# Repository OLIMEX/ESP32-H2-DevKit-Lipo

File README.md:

# ESP32-H2-DevKit-Lipo
Development board for ESP32-H2 SOC with BLE5 Matter, Thread, Zigbee

https://www.olimex.com/Products/IoT/ESP32-H2/ESP32-H2-DevKit-LiPo/open-source-hardware

Features:

* ESP32-H1-MINI-1-N4 module
* USB-C with USB to Serial converter for programming / debugging
* USB-C connected directly to ESP32-H2
* LiPo battery charger and connector
* pUEXT connector
* Qwiic/Stemma connector
* Reset button
* User button
* User LED
* all GPIOs available on two headers at 25.4 mm space
* operating temperature -40+85C
* Dimensions: 48 x 25 mm

## Licenses

* Hardware is released under CERN Open Hardware Licence Version 2 - Strongly Reciprocal, all silkscreen credits to Olimex should remain;
* Software is released under GPL3 Licensee
* Documentation is released under CC BY-SA 3.0

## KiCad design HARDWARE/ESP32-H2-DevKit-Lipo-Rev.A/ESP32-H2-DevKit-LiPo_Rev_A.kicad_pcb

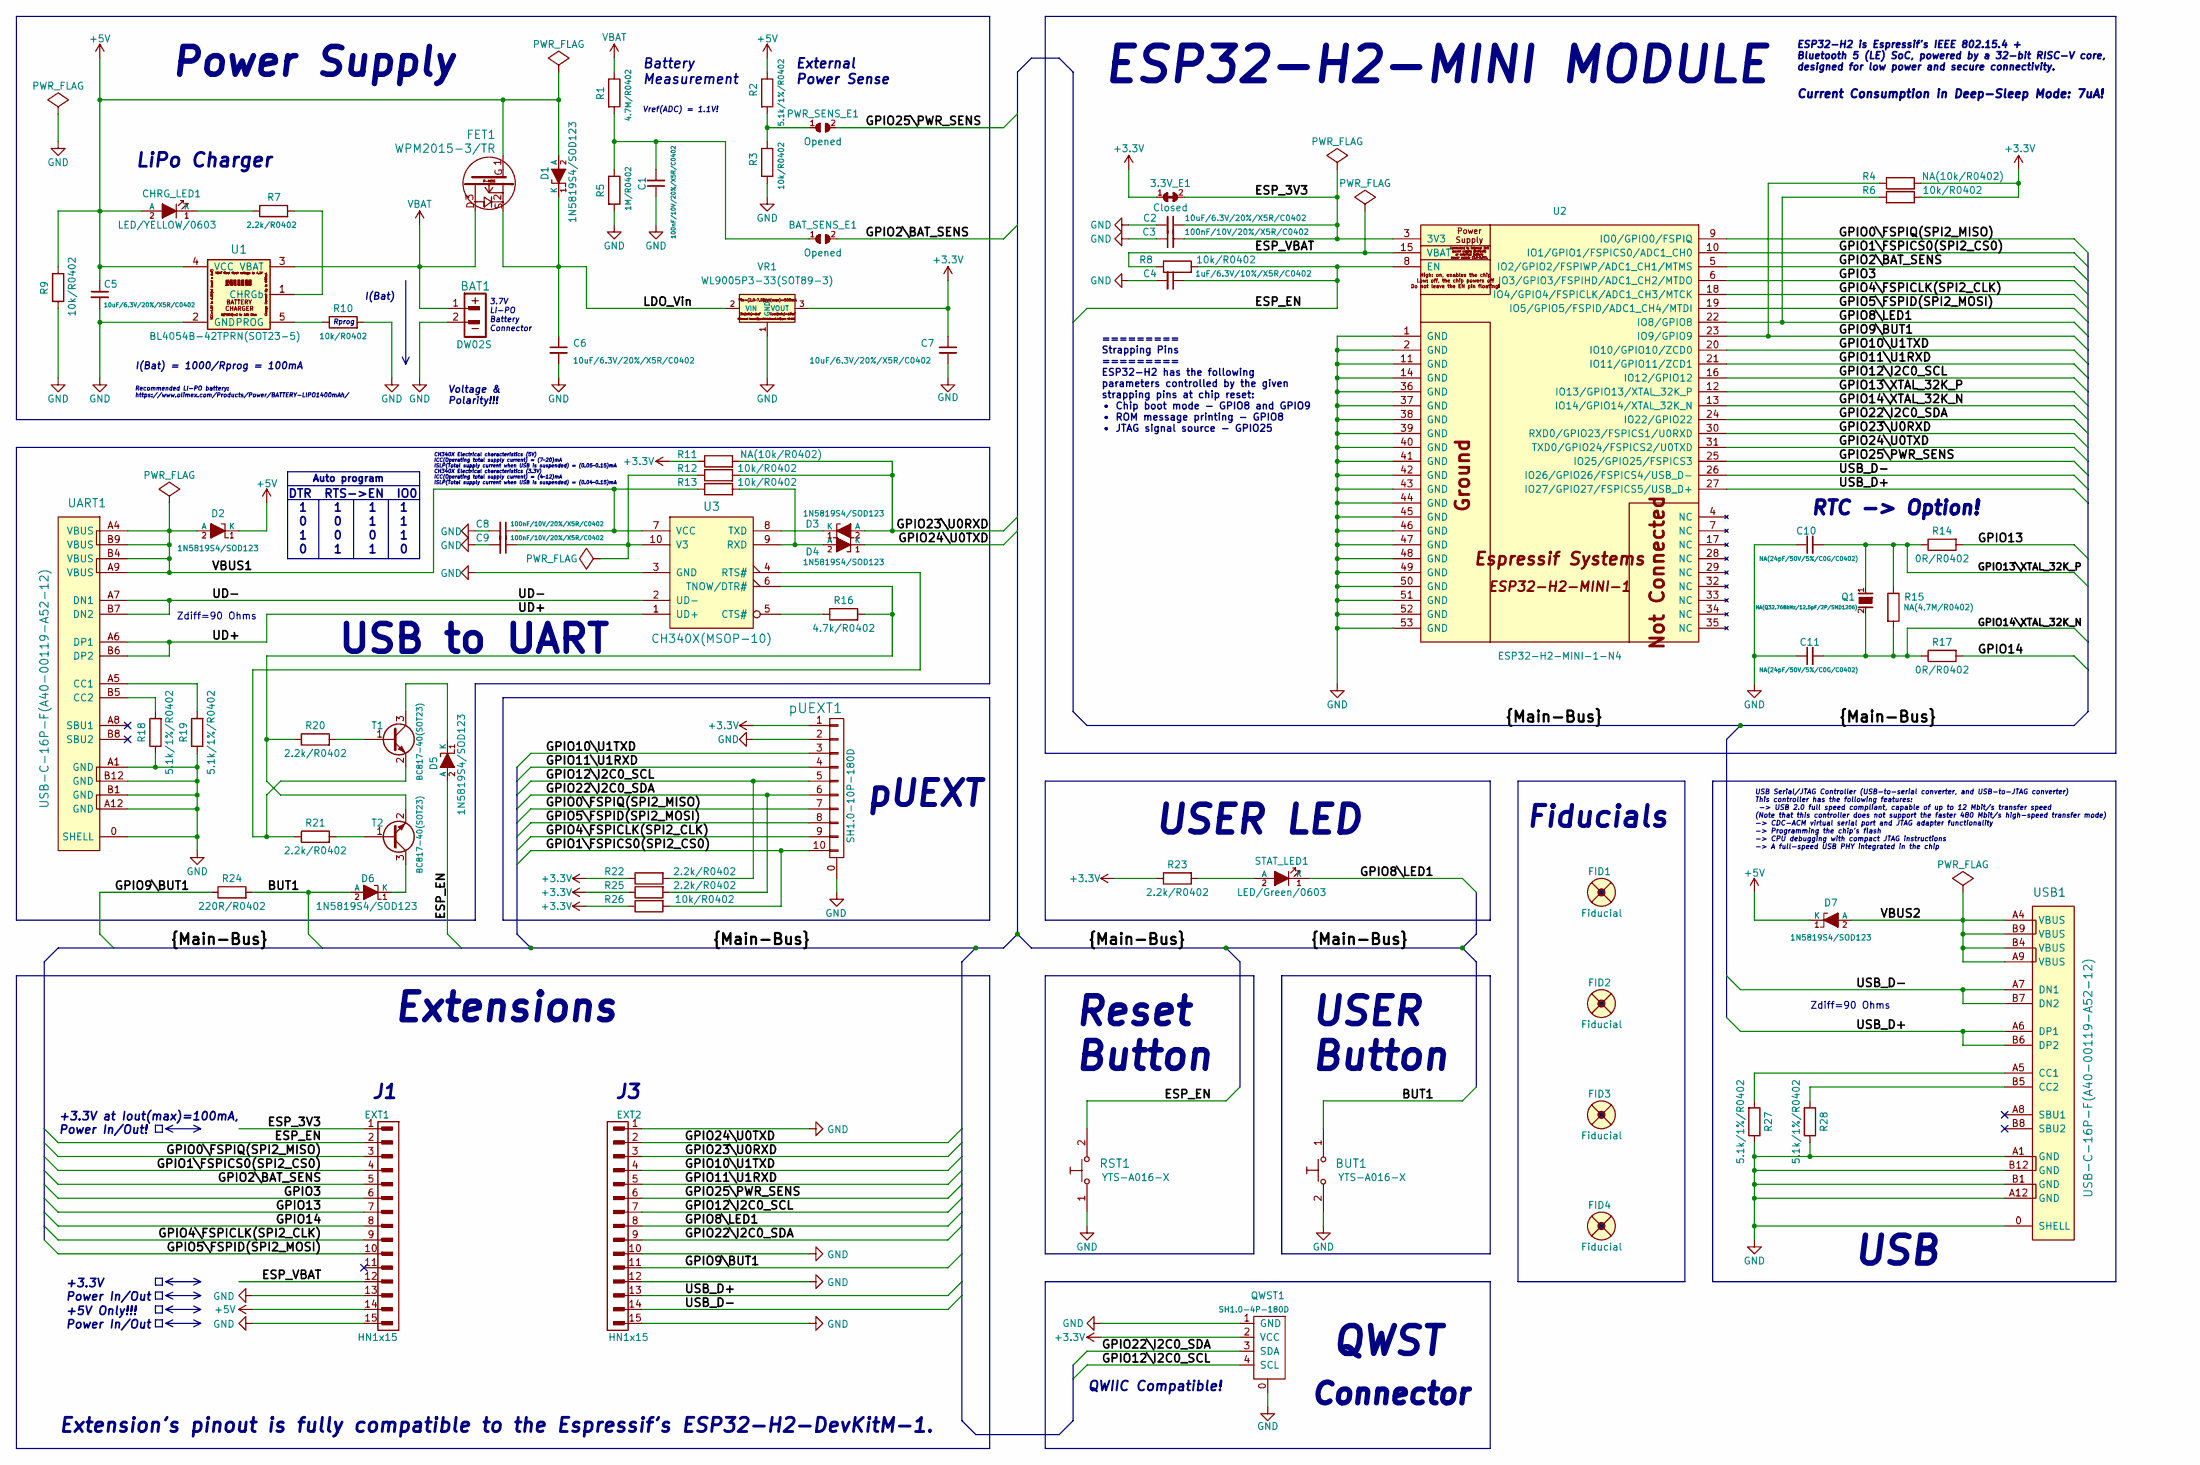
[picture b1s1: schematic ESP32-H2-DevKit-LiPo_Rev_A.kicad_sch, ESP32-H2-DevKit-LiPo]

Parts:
3.3V_E1: Closed; SJ_Closed
BAT1: DW02S; LIPO_BAT_VERTICAL_DW02S
BAT_SENS_E1: Opened; SJ
BUT1: YTS-A016-X
C1, C3, C8, C9: 100nF/10V/20%/X5R/C0402; C_0402_5MIL_DWS
C2, C5, C6, C7: 10uF/6.3V/20%/X5R/C0402; C_0402_5MIL_DWS
C4: 1uF/6.3V/10%/X5R/C0402; C_0402_5MIL_DWS
C10, C11: NA(24pF/50V/5%/C0G/C0402); C_0402_5MIL_DWS
CHRG_LED1: LED/YELLOW/0603; LED_0603_KA
D1, D2, D3, D4, D5, D6, D7: 1N5819S4/SOD123; SOD-123_1C-2A_KA
EXT1, EXT2: HN1x15
FET1: WPM2015-3/TR; SOT23
FID1, FID2, FID3: Fiducial; Fiducial1x3
FID4: Fiducial; Fiducial1x3_Paste
PWR_SENS_E1: Opened; SJ
Q1: NA(Q32.768kHz/12.5pF/2P/SMD1206); CM7V-T1A(Crystal_Package-1206_3.20x1.50x0.65mm)
QWST1: SH1.0-4P-180D; BM04B-SRSS-TB
R1: 4.7M/R0402; R_0402_5MIL_DWS
R2, R18, R19, R27, R28: 5.1k/1%/R0402; R_0402_5MIL_DWS
R3, R6, R8, R9, R10, R12, R13, R26: 10k/R0402; R_0402_5MIL_DWS
R4, R11: NA(10k/R0402); R_0402_5MIL_DWS
R5: 1M/R0402; R_0402_5MIL_DWS
R7, R20, R21, R22, R23, R25: 2.2k/R0402; R_0402_5MIL_DWS
R14, R17: 0R/R0402; R_0402_5MIL_DWS
R15: NA(4.7M/R0402); R_0402_5MIL_DWS
R16: 4.7k/R0402; R_0402_5MIL_DWS
R24: 220R/R0402; R_0402_5MIL_DWS
RST1: YTS-A016-X
STAT_LED1: LED/Green/0603; LED_0603_KA
T1, T2: BC817-40(SOT23); SOT23
U1: BL4054B-42TPRN(SOT23-5); SOT-23-5
U2: ESP32-H2-MINI-1-N4; ESP32-­C3-­MINI­-1
U3: CH340X(MSOP-10); MSOP-10_Pitch-0.5mm_3.00x3.00x1.00mm
UART1: USB-C-16P-F(A40-00119-A52-12); USB2.0_TYPE-C(A40-00119-A52-12)_Paste
USB1: USB-C-16P-F(A40-00119-A52-12); USB2.0_TYPE-C(A40-00119-A52-12)_Paste
VR1: WL9005P3-33(SOT89-3); SOT89-3
pUEXT1: SH1.0-10P-180D; BM10B-SRSS-TB

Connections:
+3.3V: 3.3V_E1.1, C7.1, QWST1.2 (VCC), R4.2, R6.1, R11.1, R22.1, R23.1, R25.1, R26.1, VR1.3 (VOUT), pUEXT1.1
+5V: C5.1, CHRG_LED1.2 (A), D1.2 (A), D2.1 (K), D7.1 (K), EXT1.14, FET1.1, R2.1, R9.1, U1.4 (VCC)
/BUT1: BUT1.1, D6.2 (A), R24.2
/ESP_3V3: 3.3V_E1.2, C2.1, C3.2, EXT1.1, U2.3 (3V3)
/ESP_EN: C4.1, D5.2 (A), EXT1.2, R8.2, RST1.2, U2.8 (EN)
/ESP_VBAT: EXT1.12, R8.1, U2.15 (VBAT)
/GPIO0\FSPIQ(SPI2_MISO): EXT1.3, U2.9 (IO0/GPIO0/FSPIQ), pUEXT1.7
/GPIO1\FSPICS0(SPI2_CS0): EXT1.4, R26.2, U2.10 (IO1/GPIO1/FSPICS0/ADC1_CH0), pUEXT1.10
/GPIO2\BAT_SENS: BAT_SENS_E1.2, EXT1.5, U2.5 (IO2/GPIO2/FSPIWP/ADC1_CH1/MTMS)
/GPIO3: EXT1.6, U2.6 (IO3/GPIO3/FSPIHD/ADC1_CH2/MTDO)
/GPIO4\FSPICLK(SPI2_CLK): EXT1.9, U2.18 (IO4/GPIO4/FSPICLK/ADC1_CH3/MTCK), pUEXT1.9
/GPIO5\FSPID(SPI2_MOSI): EXT1.10, U2.19 (IO5/GPIO5/FSPID/ADC1_CH4/MTDI), pUEXT1.8
/GPIO8\LED1: EXT2.8, R6.2, STAT_LED1.1 (K), U2.22 (IO8/GPIO8)
/GPIO9\BUT1: EXT2.11, R4.1, R24.1, U2.23 (IO9/GPIO9)
/GPIO10\U1TXD: EXT2.4, U2.20 (IO10/GPIO10/ZCD0), pUEXT1.3
/GPIO11\U1RXD: EXT2.5, U2.21 (IO11/GPIO11/ZCD1), pUEXT1.4
/GPIO12\I2C0_SCL: EXT2.7, QWST1.4 (SCL), R22.2, U2.16 (IO12/GPIO12), pUEXT1.5
/GPIO13: EXT1.7, R14.2
/GPIO13\XTAL_32K_P: C10.2, Q1.1, R14.1, R15.1, U2.12 (IO13/GPIO13/XTAL_32K_P)
/GPIO14: EXT1.8, R17.2
/GPIO14\XTAL_32K_N: C11.2, Q1.2, R15.2, R17.1, U2.13 (IO14/GPIO14/XTAL_32K_N)
/GPIO22\I2C0_SDA: EXT2.9, QWST1.3 (SDA), R25.2, U2.24 (IO22/GPIO22), pUEXT1.6
/GPIO23\U0RXD: D3.2 (A), EXT2.3, R11.2, R12.2, U2.30 (RXD0/GPIO23/FSPICS1/U0RXD)
/GPIO24\U0TXD: D4.1 (K), EXT2.2, U2.31 (TXD0/GPIO24/FSPICS2/U0TXD)
/GPIO25\PWR_SENS: EXT2.6, PWR_SENS_E1.2, U2.25 (IO25/GPIO25/FSPICS3)
/LDO_Vin: C6.1, D1.1 (K), FET1.2, VR1.2 (VIN)
/UD+: U3.1 (UD+), UART1.A6 (DP1), UART1.B6 (DP2)
/UD-: U3.2 (UD-), UART1.A7 (DN1), UART1.B7 (DN2)
/USB_D+: EXT2.13, U2.27 (IO27/GPIO27/FSPICS5/USB_D+), USB1.A6 (DP1), USB1.B6 (DP2)
/USB_D-: EXT2.14, U2.26 (IO26/GPIO26/FSPICS4/USB_D-), USB1.A7 (DN1), USB1.B7 (DN2)
/VBUS1: C8.1, D2.2 (A), R13.1, U3.7 (VCC), UART1.A4 (VBUS), UART1.A9 (VBUS), UART1.B4 (VBUS), UART1.B9 (VBUS)
/VBUS2: D7.2 (A), USB1.A4 (VBUS), USB1.A9 (VBUS), USB1.B4 (VBUS), USB1.B9 (VBUS)
GND: BAT1.2, BUT1.2, C1.1, C2.2, C3.1, C4.2, C5.2, C6.2, C7.2, C8.2, C9.2, C10.1, C11.1, EXT1.13, EXT1.15, EXT2.1, EXT2.10, EXT2.12, EXT2.15, QWST1.0, QWST1.1 (GND), R3.2, R5.2, R9.2, R10.2, R18.1, R19.1, R27.1, R28.1, RST1.1, U1.2 (GND), U2.1 (GND), U2.2 (GND), U2.11 (GND), U2.14 (GND), U2.36 (GND), U2.37 (GND), U2.38 (GND), U2.39 (GND), U2.40 (GND), U2.41 (GND), U2.42 (GND), U2.43 (GND), U2.44 (GND), U2.45 (GND), U2.46 (GND), U2.47 (GND), U2.48 (GND), U2.49 (GND), U2.50 (GND), U2.51 (GND), U2.52 (GND), U2.53 (GND), U3.3 (GND), UART1.0 (SHELL), UART1.A1 (GND), UART1.A12 (GND), UART1.B1 (GND), UART1.B12 (GND), USB1.0 (SHELL), USB1.A1 (GND), USB1.A12 (GND), USB1.B1 (GND), USB1.B12 (GND), VR1.1 (GND), pUEXT1.0, pUEXT1.2
unnamed: BAT_SENS_E1.1, C1.2, R1.2, R5.1
unnamed: CHRG_LED1.1 (K), R7.1
unnamed: D3.1 (K), U3.8 (TXD)
unnamed: D4.2 (A), R13.2, U3.9 (RXD)
unnamed: D5.1 (K), T1.3 (C)
unnamed: D6.1 (K), T2.3 (C)
unnamed: PWR_SENS_E1.1, R2.2, R3.1
unnamed: R23.2, STAT_LED1.2 (A)
unnamed: R20.2, T1.1 (B)
unnamed: R21.1, T1.2 (E), U3.4 (RTS#)
unnamed: R21.2, T2.1 (B)
unnamed: R16.2, R20.1, T2.2 (E), U3.6 (TNOW/DTR#)
unnamed: R7.2, U1.1 (CHRGb)
unnamed: R10.1, U1.5 (PROG)
unnamed: R16.1, U3.5 (CTS#)
unnamed: C9.1, R12.1, U3.10 (V3)
unnamed: R19.2, UART1.A5 (CC1)
unnamed: R18.2, UART1.B5 (CC2)
unnamed: R27.2, USB1.A5 (CC1)
unnamed: R28.2, USB1.B5 (CC2)
VBAT: BAT1.1, FET1.3, R1.1, U1.3 (VBAT)

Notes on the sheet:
pUEXT
I(Bat) = 1000/Rprog = 100mA
DTR RTS->EN IO0
I(Bat)
========= Strapping Pins ========= ESP32-H2 has the following parameters controlled by the given strapping pins at chip reset: • Chip boot mode - GPIO8 and GPIO9 • ROM message printing - GPIO8 • JTAG signal source - GPIO25
LiPo Charger
External Power Sense
USB
USB to UART
Vref(ADC) = 1.1V!
RTC -> Option!
Reset Button
Extensions
USER LED
Zdiff=90 Ohms
Fiducials
Extension's pinout is fully compatible to the Espressif's ESP32-H2-DevKitM-1.
Auto program
CH340X Electrical characteristics (5V) ICC(Operating total supply current) = (7~20)mA ISLP(Total supply current when USB is suspended) = (0.05~0.15)mA CH340X Electrical characteristics (3.3V) ICC(Operating total supply current) = (4~12)mA ISLP(Total supply current when USB is suspended) = (0.04~0.1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
+5V Only!!! Power In/Out
Rprog
Battery Measurement
QWST
ESP32-H2-MINI MODULE
USB Serial/JTAG Controller (USB-to-serial converter, and USB-to-JTAG converter) This controller has the following features: -> USB 2.0 full speed compliant, capable of up to 12 Mbit/s transfer speed (Note that this controller does not support the faster 480 Mbit/s high-speed transfer mode) -> CDC-A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
QWIIC Compatible!
3.7V LI-PO Battery Connector
Connector
ESP32-H2 is Espressif's IEEE 802.15.4 + Bluetooth 5 (LE) SoC, powered by a 32-bit RISC-V core, designed for low power and secure connectivity.
Power Supply
Voltage & Polarity!!!
+3.3V Power In/Out
Current Consumption in Deep-Sleep Mode: 7uA!
USER Button
+3.3V at Iout(max)=100mA, Power In/Out!
Recommended LI-PO battery: https://www.olimex.com/Products/Power/BATTERY-LIPO1400mAh/

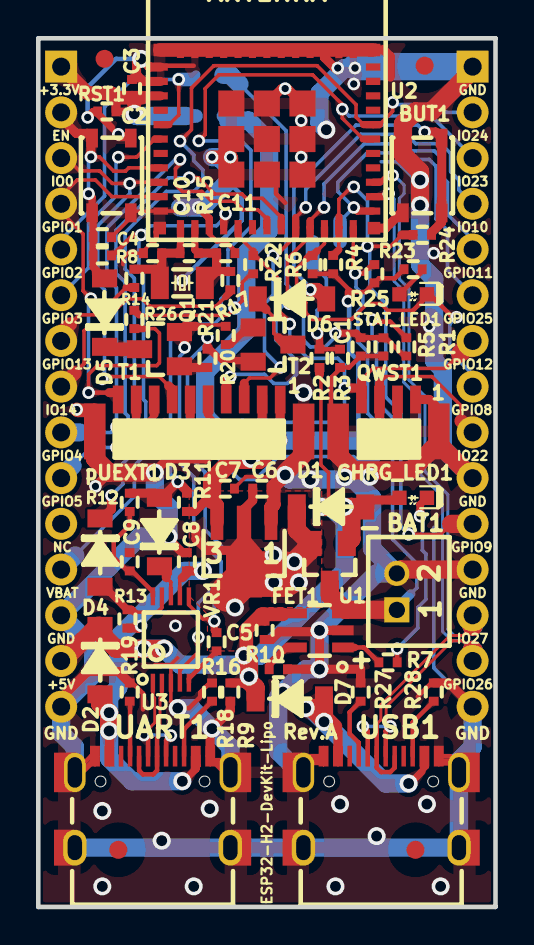
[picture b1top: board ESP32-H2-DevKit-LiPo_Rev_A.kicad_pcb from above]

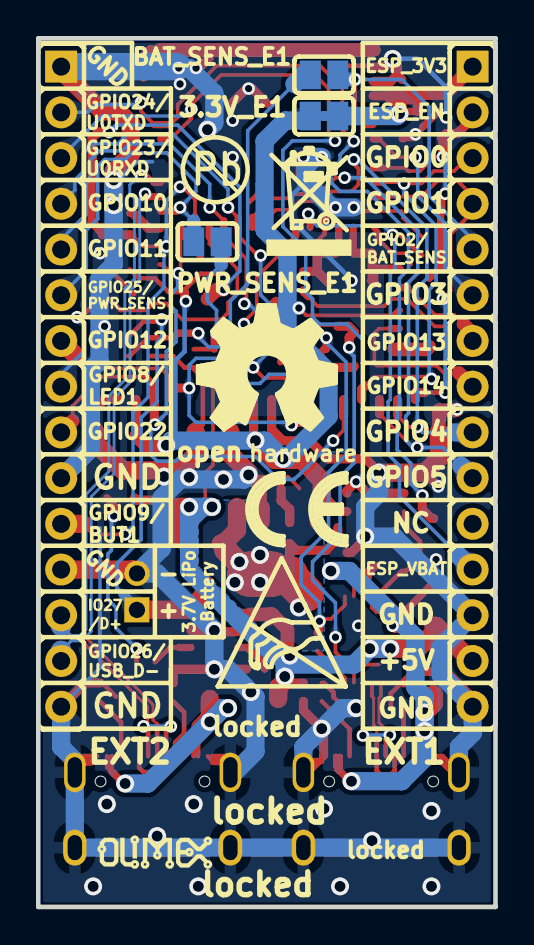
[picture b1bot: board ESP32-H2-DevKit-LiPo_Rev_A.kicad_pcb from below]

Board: 2 copper layers, 25.4 x 48.3 mm, 78 parts (11 on the bottom side), 54 nets.

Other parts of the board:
Logo_OLIMEX_80: Logo_OLIMEX_80
Sign_Antistatic: Sign_Antistatic
Sign_CE: CE_Sign
Sign_OSHW_8x8: Sign_OSHW_8x8
Sign_PB-Free: Sign_PB-Free
Sign_RecycleBin_1: Sign_RecycleBin_1

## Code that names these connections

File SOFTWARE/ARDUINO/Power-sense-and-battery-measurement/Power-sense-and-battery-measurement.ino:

// ==========================================================
// ESP32-H2-DevKit-LiPo Battery and Power Sense Demo
// ----------------------------------------------------------
// First make sure jumpers BAT_SENS_E1 and 
// PWR_SENS_E1 are closed (pads soldered together)!
//
// In Tools -> Board select ESP32H2 Dev Module and Enable CDC on boot!
//
// External Power Sense: GPIO25
// Battery Measurement:  GPIO2
// User Button (BUT1):   GPIO9
// LED:                  GPIO8
//
// Resistor divider coefficient = (R5 + R1) / R5 = 5.7
// Maximum battery voltage = 4.2V
//
// ➤ Press BUT1 for 2–6 seconds → enter ADC calibration mode
// ➤ Press BUT1 for >6 seconds → reset stored calibration factor
// ➤ Measure the battery with a multimeter *while still connected*
//    (at battery contacts on the bottom of the board)
// ➤ LED blinks fast in calibration mode and flashes 3× on success
// ➤ LED flashes 5× quickly on calibration reset
// ==========================================================

#include <Preferences.h>

#define POWER_SENSE_PIN   25
#define BATTERY_PIN       2
#define BUTTON_PIN        9
#define LED_PIN           8

// Divider ratio (R5+R1)/R5 = 5.7
float resistorCoeff = 5.7;

// ADC calibration coefficient (stored in flash)
Preferences prefs;
float calibrationFactor = 1.0;

// LED control
unsigned long lastBlink = 0;
bool ledState = false;

// Calibration mode flag
bool calibrating = false;

// Button press tracking
unsigned long buttonPressStart = 0;
bool buttonPressed = false;

// ----------------------------------------------------------
// Setup
// ----------------------------------------------------------
void setup() {
  Serial.begin(115200);
  pinMode(POWER_SENSE_PIN, INPUT);
  pinMode(BATTERY_PIN, INPUT);
  pinMode(BUTTON_PIN, INPUT_PULLUP);
  pinMode(LED_PIN, OUTPUT);

  prefs.begin("adc-calib", false);
  calibrationFactor = prefs.getFloat("factor", 1.0);

  Serial.println("\nESP32-H2-DevKit-LiPo Power & Battery Sense");
  Serial.println("------------------------------------------------");
  Serial.print("Resistor divider coefficient: ");
  Serial.println(resistorCoeff);
  Serial.print("Calibration factor: ");
  Serial.print(calibrationFactor);
  if (prefs.isKey("factor"))
    Serial.println("  (loaded from flash)");
  else
    Serial.println("  (using default)");
  Serial.println("------------------------------------------------\n");
}

// ----------------------------------------------------------
// Main loop
// ----------------------------------------------------------
void loop() {
  unsigned long now = millis();

  // LED blinking pattern
  unsigned long interval = calibrating ? 150 : 800;
  if (now - lastBlink > interval) {
    ledState = !ledState;
    digitalWrite(LED_PIN, ledState);
    lastBlink = now;
  }

  // Button press detection
  if (digitalRead(BUTTON_PIN) == LOW) {
    if (!buttonPressed) {
      buttonPressStart = now;
      buttonPressed = true;
    }
  } else {
    if (buttonPressed) {
      unsigned long pressDuration = now - buttonPressStart;

      if (pressDuration >= 2000 && pressDuration < 6000) {
        // Enter calibration mode
        startCalibration();
      } else if (pressDuration >= 6000) {
        // Reset calibration
        calibrationFactor = 1.0;
        prefs.clear();
        Serial.println("\n*** Calibration data reset! Using default = 1.0 ***");

        // Flash LED 5× to confirm reset
        for (int i = 0; i < 5; i++) {
          digitalWrite(LED_PIN, HIGH);
          delay(150);
          digitalWrite(LED_PIN, LOW);
          delay(150);
        }
      }

      buttonPressed = false;
    }
  }

  // Regular measurement mode
  if (!calibrating) {
    Serial.print("External Power Sense: ");
    Serial.println(digitalRead(POWER_SENSE_PIN));

    int mv = analogReadMilliVolts(BATTERY_PIN);
    float actualMv = mv * resistorCoeff * calibrationFactor;

    Serial.print("Battery Voltage: ");
    Serial.print(actualMv);
    Serial.println(" mV\n");
    delay(500);
  }
}

// ----------------------------------------------------------
// Calibration mode
// ----------------------------------------------------------
void startCalibration() {
  calibrating = true;
  Serial.println("\n=== ADC Calibration Mode ===");
  Serial.println("Measure the battery with a multimeter (while connected).");
  Serial.println("Enter the measured voltage in millivolts (e.g., 4120):");

  while (true) {
    if (Serial.available()) {
      String input = Serial.readStringUntil('\n');
      input.trim();
      float measuredMv = input.toFloat();

      if (measuredMv > 0) {
        int rawMv = analogReadMilliVolts(BATTERY_PIN) * resistorCoeff;
        calibrationFactor = measuredMv / rawMv;

        prefs.putFloat("factor", calibrationFactor);
        Serial.print("Calibration complete! Factor saved: ");
        Serial.println(calibrationFactor);

        // Flash LED 3× to confirm success
        for (int i = 0; i < 3; i++) {
          digitalWrite(LED_PIN, HIGH);
          delay(150);
          digitalWrite(LED_PIN, LOW);
          delay(150);
        }

        calibrating = false;
        Serial.println("Exiting calibration mode.\n");
        break;
      } else {
        Serial.println("Invalid input. Please enter numeric millivolts (e.g., 4120):");
      }
    }
  }
}

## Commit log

2024-01-19 initial upload
2025-10-22 New demo
    Power sense and battery measurement advanced demo
2026-03-09 Create LED-button-demo.ino
    Simple LED and button demo
2026-03-10 Update
    Added serial output demo
2026-03-10 Update
    Added platformio json and ini

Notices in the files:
HARDWARE/ESP32-H2-DevKit-Lipo-Rev.A/ESP32-H2-DevKit-LiPo_Rev_A.kicad_pcb:
(C) 2023
